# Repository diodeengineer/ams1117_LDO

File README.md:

# AMS1117 3.3V Regulator Module (LDO)

This is a simple **3.3V linear voltage regulator board** based on the **AMS1117-3.3**. It converts 5V input to 3.3V output and can be used to power ESP8266, ESP32, sensors, and other 3.3V logic devices.

## Features

- Input Voltage: 4.5V to 6.5V (typically 5V)
- Output Voltage: Fixed 3.3V
- Max Output Current: ~800mA (with proper heat dissipation)
- Low dropout (LDO): ~1.1V typical
- PCB designed in **KiCad**

## Pinout

| Pin | Description     |
|-----|-----------------|
| IN  | 5V Input        |
| GND | Ground          |
| OUT | 3.3V Output     |

## Usage

- Connect 5V to `IN`, Ground to `GND`
- You’ll get regulated 3.3V at the `OUT` pin
- Use decoupling capacitors for stability (e.g., 10uF and 22uF at IN and OUT resp.)

## Files Included

- KiCad project files (`.kicad_pcb`, `.sch`, etc.)
- Gerber files for fabrication
- Schematic PDF
- Board render 

## Preview

---

---

For powering ESPs and low-voltage devices

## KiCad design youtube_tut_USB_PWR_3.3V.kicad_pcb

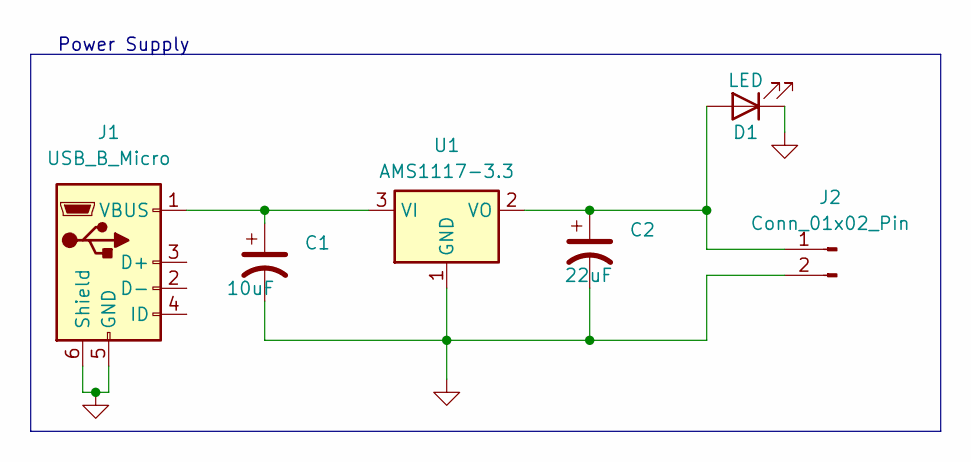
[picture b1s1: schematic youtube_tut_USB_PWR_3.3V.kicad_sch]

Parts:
C1: 10uF; CP_Radial_D6.3mm_P2.50mm
C2: 22uF; CP_Radial_D10.0mm_P5.00mm
D1: LED; LED_0402_1005Metric_Pad0.77x0.64mm_HandSolder
J1: USB_B_Micro; USB_Micro-AB_Molex_47590-0001
J2: Conn_01x02_Pin; PinHeader_1x02_P2.54mm_Vertical
U1: AMS1117-3.3; SOT-223-3_TabPin2

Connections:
GND: C1.2, C2.2, D1.1 (K), J1.5 (GND), J1.6 (Shield), J2.2, U1.1 (GND)
unnamed: C2.1, D1.2 (A), J2.1, U1.2 (VO)
unnamed: C1.1, J1.1 (VBUS), U1.3 (VI)

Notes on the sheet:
Power Supply

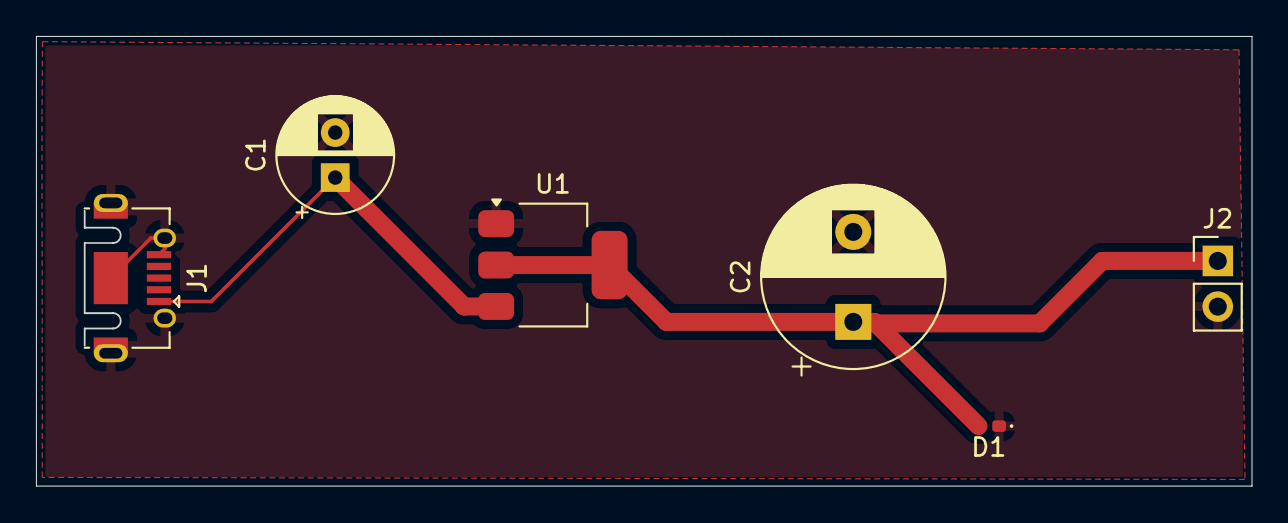
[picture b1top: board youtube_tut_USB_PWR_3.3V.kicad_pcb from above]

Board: 2 copper layers, 67.5 x 24.9 mm, 6 parts (0 on the bottom side), 3 nets.
